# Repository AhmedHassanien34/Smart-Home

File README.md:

<h1 align="center">Smart Home with Solar Tracking System</h1>

**Done by:**

1. Ahmed Mohamed Mohamed (Ahmedtorres2000@gmail.com)
2. Mohamed Yasser Elkot (my557364@gmail.com)
3. Jasmin Saber Abd-Elqader (yasmynsabralsyd@gmail.com)
4. Ahmed Bahgat Nagy (ahmedmat60@gmail.com)
5. Amir Mohamed Hassan (@gmail.com)

**Under the supervision:**
Dr. Mohamed Mahmoud Abdelwahab (‪engmohmah1961@gmail.com‬‏)

## 🔬 What is next ?

This project will be always improved this project.
So, if you have any suggestion, create an issue <a href="https://github.com/AhmedTorres2000/Smart-Home/issues">here</a></strong> and I will appreciate it.

---

## 💁‍♂️ Contribute

If you want to contribute to the project, you can:

1. Fork the project on your GitHub account.
2. Develop the project on your own.
3. Send a pull request to the project on GitHub.
4. I will review your pull request and add it to the project.

---

## 📞 Contact me

<p>  </p>

## 🔏 Credits

All credits and external sources are listed inside the page and inside this repo, references themselves.

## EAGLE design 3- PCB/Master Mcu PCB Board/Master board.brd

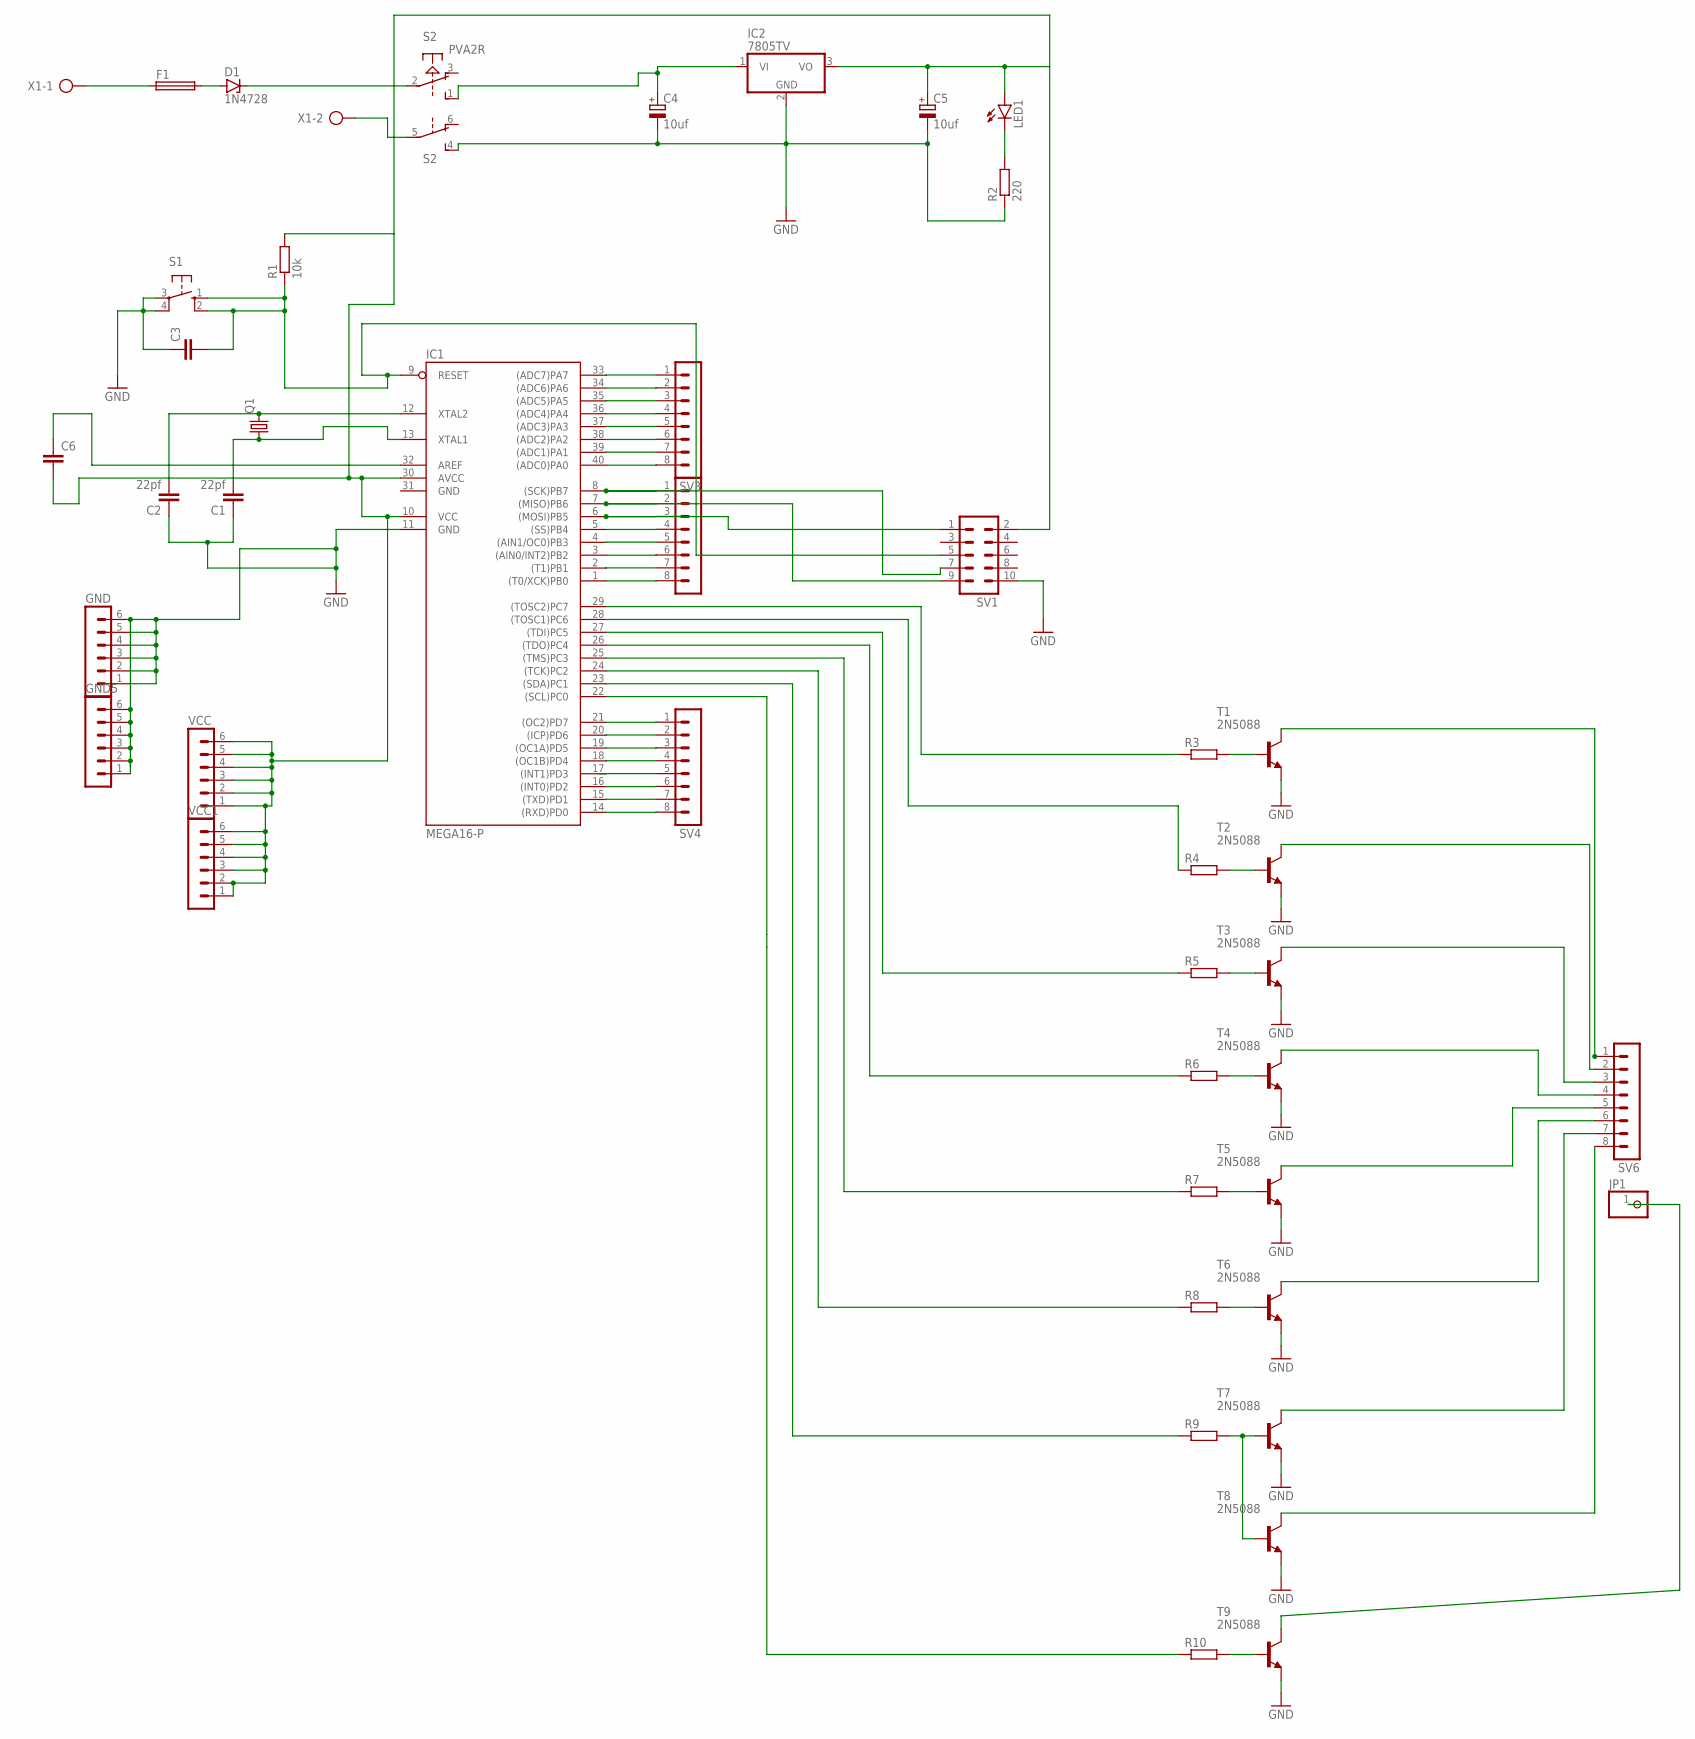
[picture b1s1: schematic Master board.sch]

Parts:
C1, C2: 22pf; C025-025X050
C3, C6: C-EU025-025X050; C025-025X050
C4, C5: 10uf; E2,5-6
D1: 1N4728; DO41Z10
F1: GSH15
GND, GND5: MA06-1
IC1: MEGA16-P; DIL40
IC2: 7805TV; TO220V
JP1: PINHD-1X1; 1X01
LED1: LED5MM
Q1: CRYSTALHC49U70; HC49U70
R1: 10k; 0207/10
R2: 220; 0207/10
R3, R4, R5, R6, R7, R8, R9, R10: R-EU_0207/10; 0207/10
S1: 10-XX; B3F-10XX
S2: PVA2R
SV1: MA05-2
SV3, SV4, SV5, SV6: MA08-1W
T1, T2, T3, T4, T5, T6, T7, T8, T9: 2N5088; TO92
VCC, VCC1: MA06-1
X1: AK500/2

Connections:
GND: C1.1, C2.1, C3.1, C4.-, C5.-, GND.1, GND.2, GND.3, GND.4, GND.5, GND.6, GND5.1, GND5.2, GND5.3, GND5.4, GND5.5, GND5.6, IC1.11 (GND), IC1.31 (GND), IC2.2 (GND), R2.1, S1.3, S1.4 (P1), S2.4 (S), SV1.10, T1.3 (E), T2.3 (E), T3.3 (E), T4.3 (E), T5.3 (E), T6.3 (E), T7.3 (E), T8.3 (E), T9.3 (E)
unnamed: C1.2, IC1.13 (XTAL1), Q1.1
unnamed: C2.2, IC1.12 (XTAL2), Q1.2
unnamed: IC1.6 ((MOSI)PB5), SV1.1, SV5.3
unnamed: IC1.7 ((MISO)PB6), SV1.9, SV5.2
unnamed: IC1.8 ((SCK)PB7), SV1.7, SV5.1
unnamed: C4.+, IC2.1 (VI), S2.1 (S)
unnamed: IC1.21 ((OC2)PD7), SV4.1
unnamed: LED1.K (C), R2.2
unnamed: IC1.33 ((ADC7)PA7), SV3.1
unnamed: IC1.34 ((ADC6)PA6), SV3.2
unnamed: IC1.35 ((ADC5)PA5), SV3.3
unnamed: IC1.36 ((ADC4)PA4), SV3.4
unnamed: IC1.20 ((ICP)PD6), SV4.2
unnamed: D1.A, F1.2
unnamed: F1.1, X1.1
unnamed: D1.C, S2.2
unnamed: IC1.19 ((OC1A)PD5), SV4.3
unnamed: S2.5, X1.2
unnamed: IC1.29 ((TOSC2)PC7), R3.1
unnamed: IC1.28 ((TOSC1)PC6), R4.1
unnamed: IC1.23 ((SDA)PC1), R9.1
unnamed: IC1.27 ((TDI)PC5), R5.1
unnamed: IC1.26 ((TDO)PC4), R6.1
unnamed: IC1.25 ((TMS)PC3), R7.1
unnamed: IC1.22 ((SCL)PC0), R10.1
unnamed: IC1.37 ((ADC3)PA3), SV3.5
unnamed: IC1.38 ((ADC2)PA2), SV3.6
unnamed: IC1.39 ((ADC1)PA1), SV3.7
unnamed: IC1.40 ((ADC0)PA0), SV3.8
unnamed: IC1.18 ((OC1B)PD4), SV4.4
unnamed: C6.1, IC1.32 (AREF)
unnamed: IC1.17 ((INT1)PD3), SV4.5
unnamed: IC1.16 ((INT0)PD2), SV4.6
unnamed: IC1.15 ((TXD)PD1), SV4.7
unnamed: IC1.14 ((RXD)PD0), SV4.8
unnamed: IC1.5 ((SS)PB4), SV5.4
unnamed: IC1.4 ((AIN1/OC0)PB3), SV5.5
unnamed: IC1.3 ((AIN0/INT2)PB2), SV5.6
unnamed: C5.+, C6.2, IC1.10 (VCC), IC1.30 (AVCC), IC2.3 (VO), LED1.A, R1.2, SV1.2, VCC.1, VCC.2, VCC.3, VCC.4, VCC.5, VCC.6, VCC1.1, VCC1.2, VCC1.3, VCC1.4, VCC1.5, VCC1.6
unnamed: IC1.2 ((T1)PB1), SV5.7
unnamed: IC1.1 ((T0/XCK)PB0), SV5.8
unnamed: R4.2, T2.2 (B)
unnamed: R5.2, T3.2 (B)
unnamed: R3.2, T1.2 (B)
unnamed: R6.2, T4.2 (B)
unnamed: R7.2, T5.2 (B)
unnamed: IC1.24 ((TCK)PC2), R8.1
unnamed: R8.2, T6.2 (B)
unnamed: R9.2, T7.2 (B), T8.2 (B)
unnamed: R10.2, T9.2 (B)
unnamed: SV6.2, T2.1 (C)
unnamed: SV6.3, T3.1 (C)
unnamed: SV6.4, T4.1 (C)
unnamed: SV6.5, T5.1 (C)
unnamed: SV6.1, T1.1 (C)
unnamed: SV6.6, T6.1 (C)
unnamed: SV6.7, T7.1 (C)
unnamed: SV6.8, T8.1 (C)
unnamed: JP1.1, T9.1 (C)

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
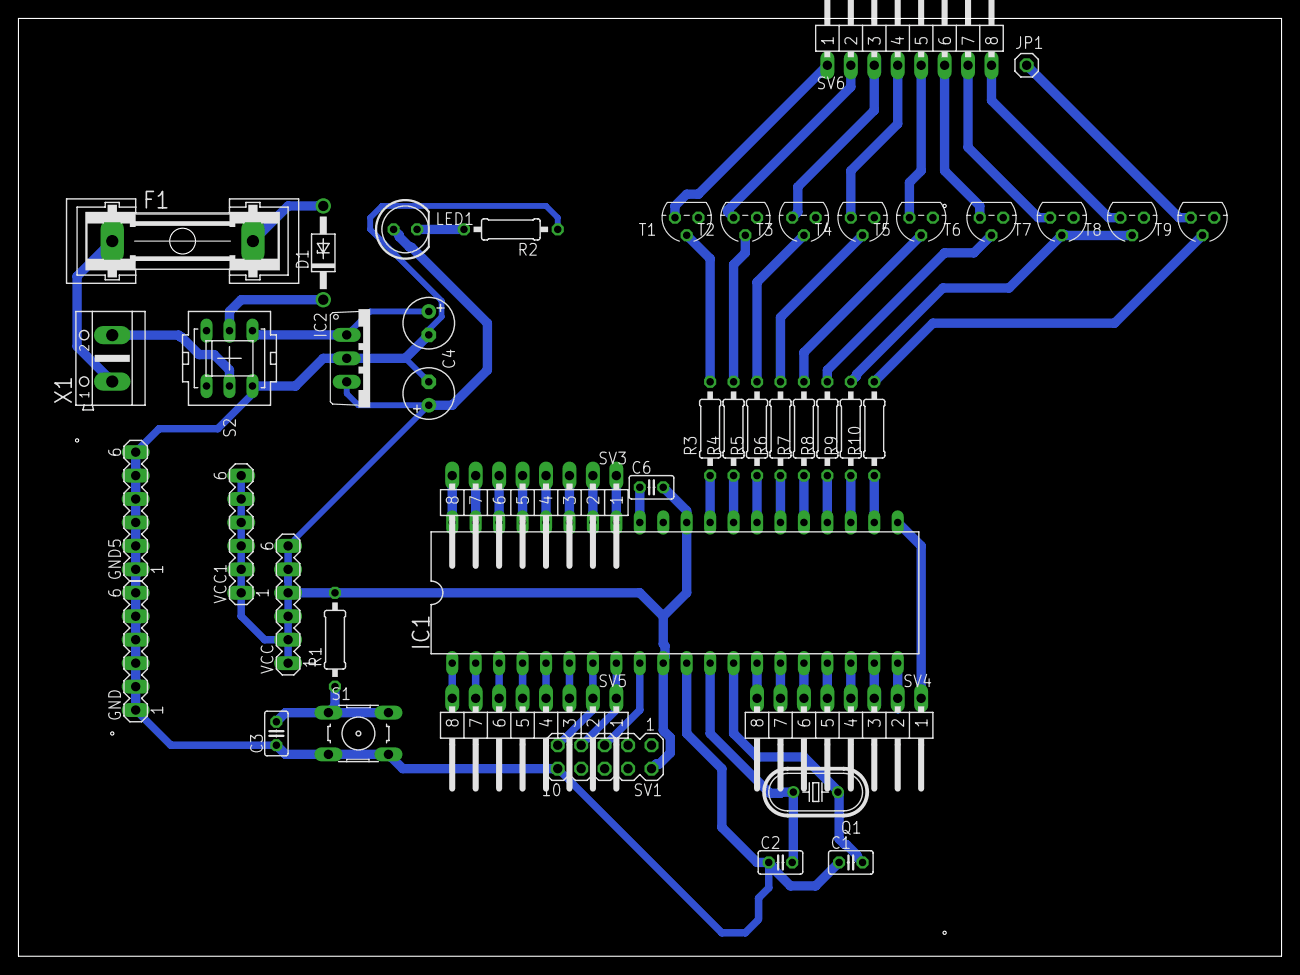
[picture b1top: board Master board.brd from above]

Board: 2 copper layers, 136.8 x 101.6 mm, 44 parts (0 on the bottom side), 62 nets.

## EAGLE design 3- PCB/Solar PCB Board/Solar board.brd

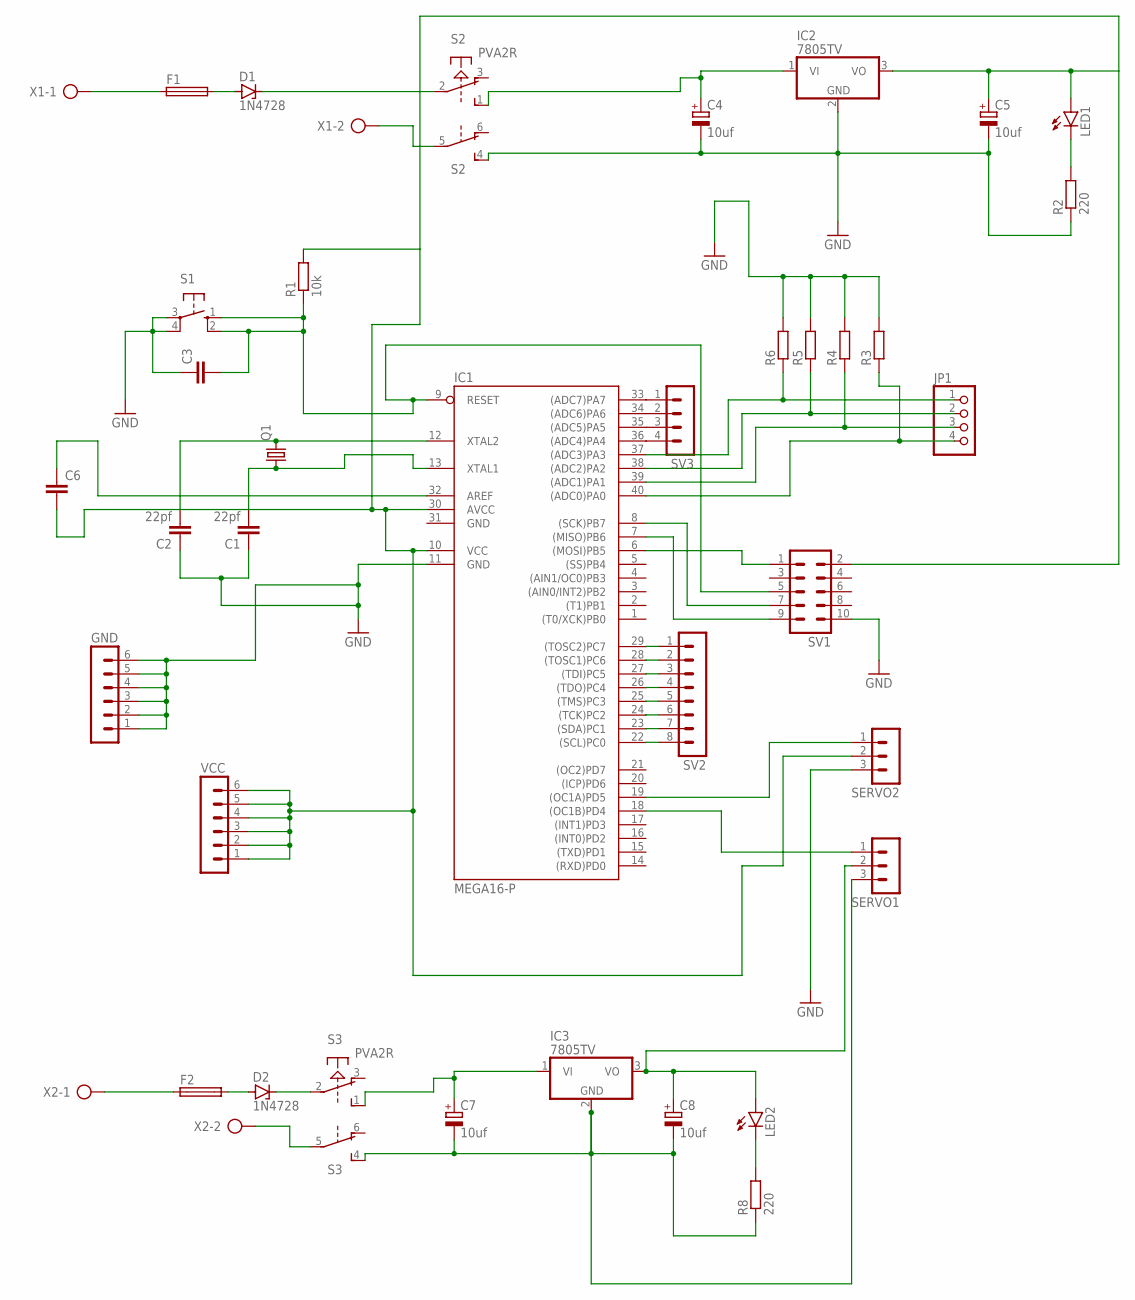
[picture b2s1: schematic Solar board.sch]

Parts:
C1, C2: 22pf; C025-025X050
C3, C6: C-EU025-025X050; C025-025X050
C4, C5, C7, C8: 10uf; E2,5-6
D1, D2: 1N4728; DO41Z10
F1, F2: GSH15
GND: MA06-1
IC1: MEGA16-P; DIL40
IC2, IC3: 7805TV; TO220V
JP1: PINHD-1X4; 1X04
LED1, LED2: LED5MM
Q1: CRYSTALHC49U70; HC49U70
R1: 10k; 0207/10
R2, R8: 220; 0207/10
R3, R4, R5, R6: R-EU_0207/10; 0207/10
S1: 10-XX; B3F-10XX
S2, S3: PVA2R
SERVO1, SERVO2: MA03-1
SV1: MA05-2
SV2: MA08-1W
SV3: MA04-1
VCC: MA06-1
X1, X2: AK500/2

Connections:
GND: C1.1, C2.1, C3.1, C4.-, C5.-, GND.1, GND.2, GND.3, GND.4, GND.5, GND.6, IC1.11 (GND), IC1.31 (GND), IC2.2 (GND), R2.1, R3.2, R4.2, R5.2, R6.2, S1.3, S1.4 (P1), S2.4 (S), SERVO2.3, SV1.10
unnamed: C1.2, IC1.13 (XTAL1), Q1.1
unnamed: C2.2, IC1.12 (XTAL2), Q1.2
unnamed: IC1.6 ((MOSI)PB5), SV1.1
unnamed: IC1.7 ((MISO)PB6), SV1.9
unnamed: IC1.8 ((SCK)PB7), SV1.7
unnamed: C4.+, IC2.1 (VI), S2.1 (S)
unnamed: IC1.18 ((OC1B)PD4), SERVO1.1
unnamed: C3.2, IC1.9 (RESET), R1.1, S1.1 (S), S1.2 (S1), SV1.5
unnamed: LED1.K (C), R2.2
unnamed: IC1.37 ((ADC3)PA3), JP1.1, R6.1
unnamed: IC1.38 ((ADC2)PA2), JP1.2, R5.1
unnamed: IC1.39 ((ADC1)PA1), JP1.3, R4.1
unnamed: IC1.40 ((ADC0)PA0), JP1.4, R3.1
unnamed: IC1.19 ((OC1A)PD5), SERVO2.1
unnamed: D1.A, F1.2
unnamed: F1.1, X1.1
unnamed: D1.C, S2.2
unnamed: LED2.K (C), R8.2
unnamed: S2.5, X1.2
unnamed: IC1.29 ((TOSC2)PC7), SV2.1
unnamed: IC1.28 ((TOSC1)PC6), SV2.2
unnamed: IC1.27 ((TDI)PC5), SV2.3
unnamed: IC1.26 ((TDO)PC4), SV2.4
unnamed: IC1.25 ((TMS)PC3), SV2.5
unnamed: IC1.24 ((TCK)PC2), SV2.6
unnamed: IC1.23 ((SDA)PC1), SV2.7
unnamed: IC1.22 ((SCL)PC0), SV2.8
unnamed: IC1.33 ((ADC7)PA7), SV3.1
unnamed: IC1.34 ((ADC6)PA6), SV3.2
unnamed: IC1.35 ((ADC5)PA5), SV3.3
unnamed: IC1.36 ((ADC4)PA4), SV3.4
unnamed: C7.+, IC3.1 (VI), S3.1 (S)
unnamed: C6.1, IC1.32 (AREF)
unnamed: C8.+, IC3.3 (VO), LED2.A, SERVO1.2
unnamed: S3.5, X2.2
unnamed: D2.A, F2.2
unnamed: F2.1, X2.1
unnamed: D2.C, S3.2
unnamed: C7.-, C8.-, IC3.2 (GND), R8.1, S3.4 (S), SERVO1.3
unnamed: C5.+, C6.2, IC1.10 (VCC), IC1.30 (AVCC), IC2.3 (VO), LED1.A, R1.2, SERVO2.2, SV1.2, VCC.1, VCC.2, VCC.3, VCC.4, VCC.5, VCC.6

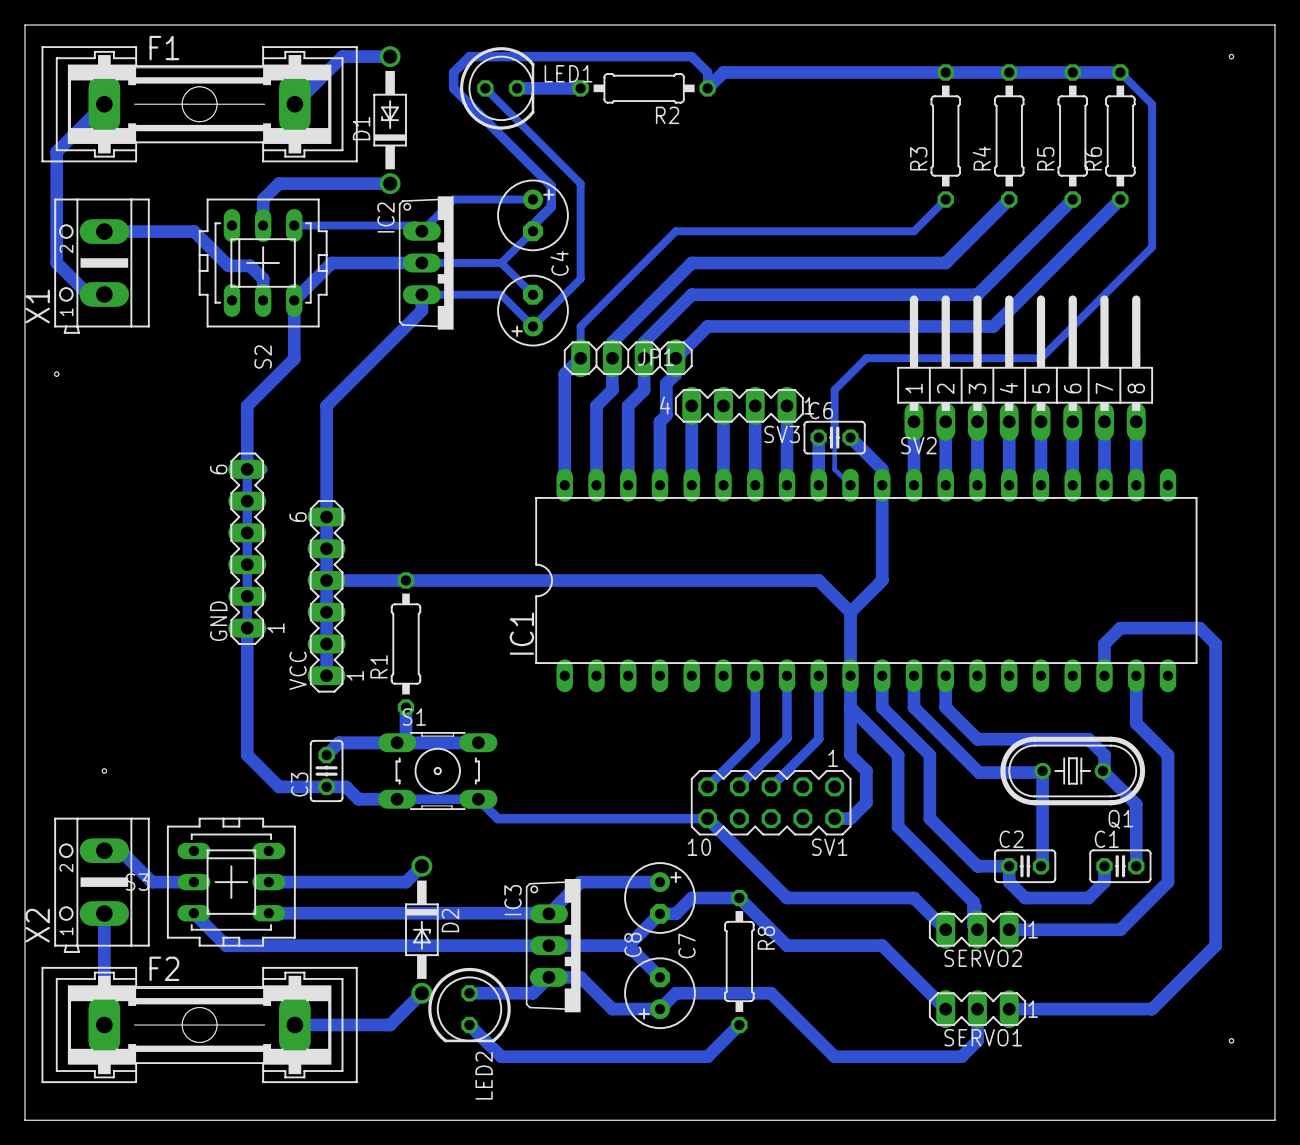
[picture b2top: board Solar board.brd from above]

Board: 2 copper layers, 100.0 x 87.6 mm, 38 parts (0 on the bottom side), 41 nets.

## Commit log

2023-08-14 Grad Project
2023-08-14 Master
2023-08-14 Slave
